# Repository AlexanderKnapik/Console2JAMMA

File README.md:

# Console2JAMMA

A system to plug video game consoles into a JAMMA arcade system. 

## Features & Goals
- SCART based RGB or VGA video input. Will work perfectly with any natively RGB or modded console, including the Dreamcast. Handles any sync stripping and CSYNC combination for you with amplified video.
- Works with any arcade cabinet supporting standard JAMMA, "CHAMMA" and the CPS2 kick harness.
- Stereo audio input with selectable mono audio combiner for the JAMMA edge, or an external stereo audio output. Amplified for up to 5 Watts of power and can handle standard arcade 4 Ohm or 8 Ohm speakers.
- Can drive 2 player controller ports for 5V or 3.3V based consoles. Will work with any console that has 12 or fewer IO lines with a modded controller port extension.
- Handy spring terminal controller adapters available for those not comfortable with soldering.
- Single player USB output to support PS3 or XBox360 too.

## Progress
This is still heavily a work in progress. I've built up the first hardware prototype and identified some issues that I would like to address. However I am mainly still testing the hardware.

There is also no firmware currently written yet. This is what would need to be addressed next before any further hardware prototypes are designed.

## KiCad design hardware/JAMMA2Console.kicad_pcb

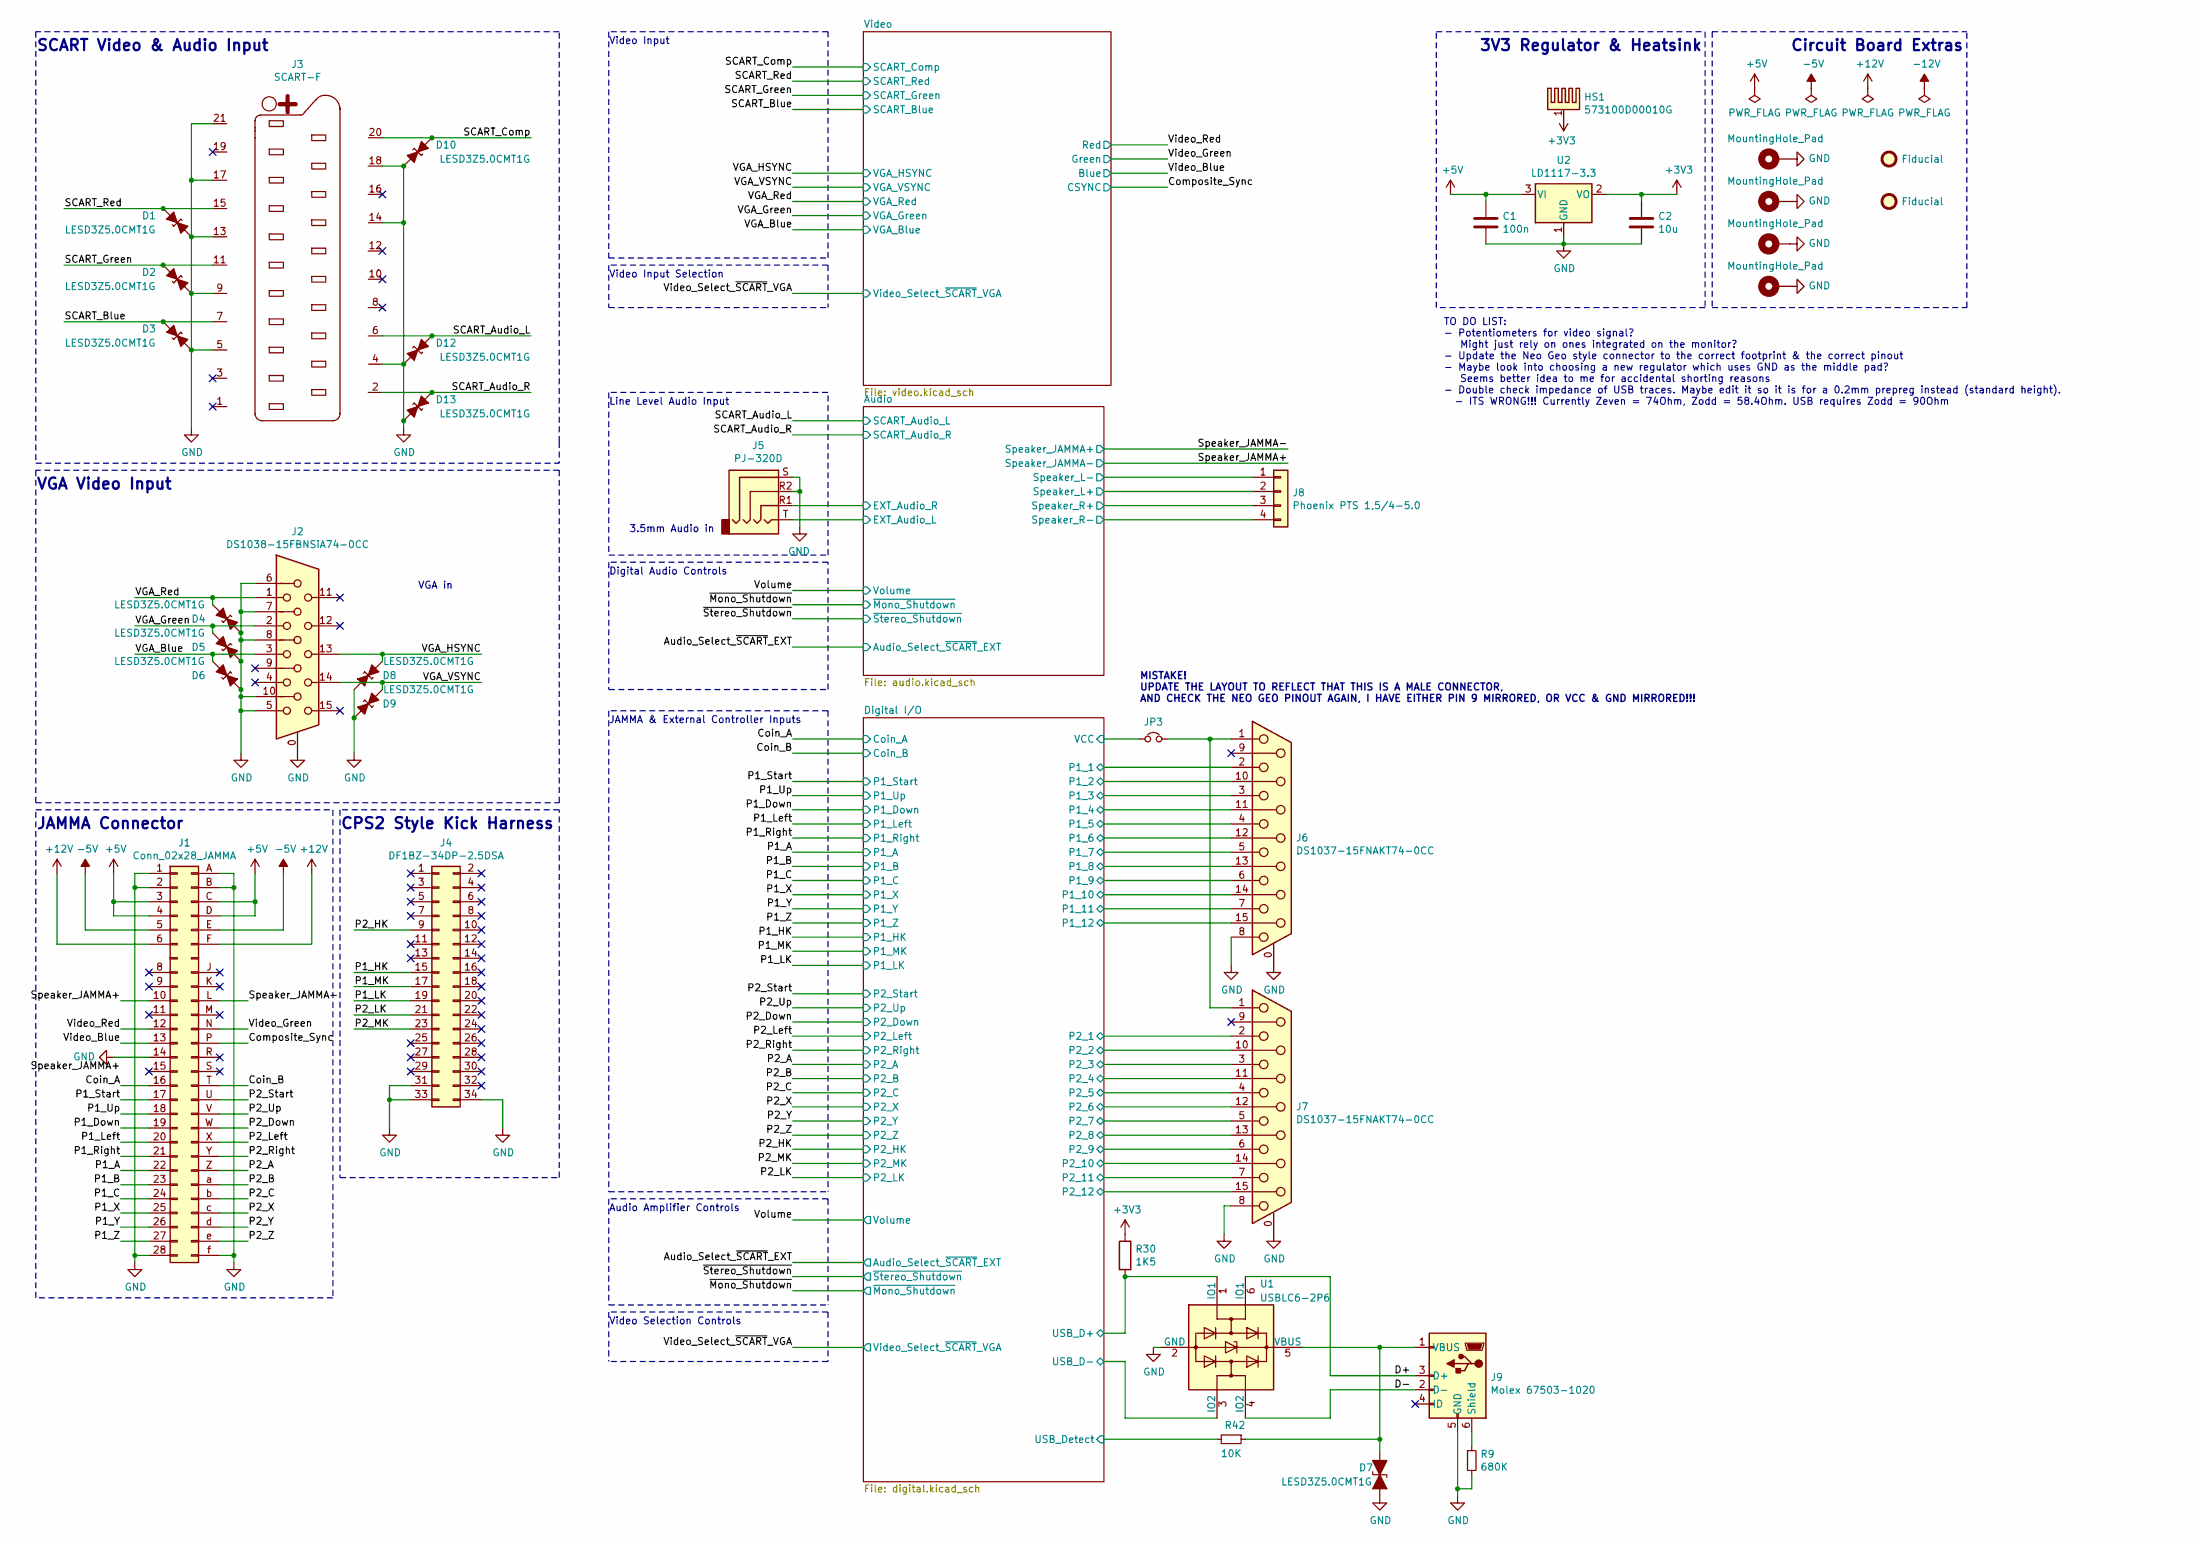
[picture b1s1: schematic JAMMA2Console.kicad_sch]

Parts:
C1: 100n; C_0603_1608Metric
C2: 10u; C_0805_2012Metric
D1, D2, D3, D4, D5, D6, D7, D8, D9, D10, D12, D13: LESD3Z5.0CMT1G; D_SOD-323
FID1, FID2: Fiducial; Fiducial_0.5mm_Mask1mm
H1, H2, H3, H4: MountingHole_Pad; MountingHole_3.2mm_M3_Pad_Via
HS1: 573100D00010G; Heatsink_AAVID_573100D000x0G_TO-252
J1: Conn_02x28_JAMMA; JAMMA_56_2x28_P3.96mm
J2: DS1038-15FBNSiA74-0CC; DSUB-15-HD_Female_Horizontal_P2.29x1.98mm_EdgePinOffset8.63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
J3: SCART-F; Conn_SCART_CS-107_Right_Angle_Female
J4: DF1BZ-34DP-2.5DSA; Conn_02x17_DF1BZ-34DP-2.5DSA
J5: PJ-320D; Jack_3.5mm_PJ320D_Horizontal
J6, J7: DS1037-15FNAKT74-0CC; DSUB-15_Female_Horizontal_P2.77x2.84mm_EdgePinOffset8.10mm_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
J8: Phoenix PTS 1,5/4-5.0; PhoenixContact_PTS_1,5_4-5_1x4_P5.00mm_Horizontal
J9: Molex 67503-1020; USB_Mini-B_Molex_657031020_Horizontal
JP3: Jumper_NC_Small; SolderJumper-2_P1.3mm_Open_TrianglePad1.0x1.5mm
R9: 680K; R_0603_1608Metric
R30: 1K5; R_0603_1608Metric
R42: 10K; R_0603_1608Metric
U1: USBLC6-2P6; SOT-666
U2: LD1117-3.3; TO-252-2

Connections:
+3V3: C2.1, HS1.1, R30.1, U2.2 (VO); also elsewhere on the board
+5V: C1.1, J1.3, J1.4, J1.C, J1.D, U2.3 (VI); also elsewhere on the board
+12V: J1.6, J1.F; also elsewhere on the board
-5V: J1.5, J1.E; also elsewhere on the board
/Coin_A: J1.16; also elsewhere on the board
/Coin_B: J1.T; also elsewhere on the board
/Composite_Sync: J1.P; also elsewhere on the board
/D+: J9.3 (D+), U1.6 (IO1)
/D-: J9.2 (D-), U1.4 (IO2)
/EXT_Audio_L: J5.T; also elsewhere on the board
/EXT_Audio_R: J5.R1; also elsewhere on the board
/P1_1: J6.2; also elsewhere on the board
/P1_2: J6.10; also elsewhere on the board
/P1_3: J6.3; also elsewhere on the board
/P1_4: J6.11 (P111); also elsewhere on the board
/P1_5: J6.4; also elsewhere on the board
/P1_6: J6.12; also elsewhere on the board
/P1_7: J6.5; also elsewhere on the board
/P1_8: J6.13; also elsewhere on the board
/P1_9: J6.6; also elsewhere on the board
/P1_10: J6.14; also elsewhere on the board
/P1_11: J6.7; also elsewhere on the board
/P1_12: J6.15; also elsewhere on the board
/P1_A: J1.22; also elsewhere on the board
/P1_B: J1.23; also elsewhere on the board
/P1_C: J1.24; also elsewhere on the board
/P1_Down: J1.19; also elsewhere on the board
/P1_HK: J4.15; also elsewhere on the board
/P1_LK: J4.19; also elsewhere on the board
/P1_Left: J1.20; also elsewhere on the board
/P1_MK: J4.17; also elsewhere on the board
/P1_Right: J1.21; also elsewhere on the board
/P1_Start: J1.17; also elsewhere on the board
/P1_Up: J1.18; also elsewhere on the board
/P1_X: J1.25; also elsewhere on the board
/P1_Y: J1.26; also elsewhere on the board
/P1_Z: J1.27; also elsewhere on the board
/P2_1: J7.2; also elsewhere on the board
/P2_2: J7.10; also elsewhere on the board
/P2_3: J7.3; also elsewhere on the board
/P2_4: J7.11 (P111); also elsewhere on the board
/P2_5: J7.4; also elsewhere on the board
/P2_6: J7.12; also elsewhere on the board
/P2_7: J7.5; also elsewhere on the board
/P2_8: J7.13; also elsewhere on the board
/P2_9: J7.6; also elsewhere on the board
/P2_10: J7.14; also elsewhere on the board
/P2_11: J7.7; also elsewhere on the board
/P2_12: J7.15; also elsewhere on the board
/P2_A: J1.Z; also elsewhere on the board
/P2_B: J1.a; also elsewhere on the board
/P2_C: J1.b; also elsewhere on the board
/P2_Down: J1.W; also elsewhere on the board
/P2_HK: J4.9; also elsewhere on the board
/P2_LK: J4.21; also elsewhere on the board
/P2_Left: J1.X; also elsewhere on the board
/P2_MK: J4.23; also elsewhere on the board
/P2_Right: J1.Y; also elsewhere on the board
/P2_Start: J1.U; also elsewhere on the board
/P2_Up: J1.V; also elsewhere on the board
/P2_X: J1.c; also elsewhere on the board
/P2_Y: J1.d; also elsewhere on the board
/P2_Z: J1.e; also elsewhere on the board
/SCART_Audio_L: D12.1, J3.6; also elsewhere on the board
/SCART_Audio_R: D13.1, J3.2; also elsewhere on the board
/SCART_Blue: D3.1, J3.7; also elsewhere on the board
/SCART_Comp: D10.1, J3.20; also elsewhere on the board
/SCART_Green: D2.1, J3.11; also elsewhere on the board
/SCART_Red: D1.1, J3.15; also elsewhere on the board
/Speaker_JAMMA+: J1.10; also elsewhere on the board
/Speaker_JAMMA-: J1.L; also elsewhere on the board
/Speaker_L+: J8.2; also elsewhere on the board
/Speaker_L-: J8.1; also elsewhere on the board
/Speaker_R+: J8.3; also elsewhere on the board
/Speaker_R-: J8.4; also elsewhere on the board
/USB_D+: R30.2, U1.1 (IO1); also elsewhere on the board
/USB_D-: U1.3 (IO2); also elsewhere on the board
/USB_Detect: R42.2; also elsewhere on the board
/VCC: JP3.2; also elsewhere on the board
/VGA_Blue: D6.2, J2.3; also elsewhere on the board
/VGA_Green: D5.2, J2.2; also elsewhere on the board
/VGA_HSYNC: D8.2, J2.13; also elsewhere on the board
/VGA_Red: D4.2, J2.1; also elsewhere on the board
/VGA_VSYNC: D9.2, J2.14; also elsewhere on the board
/Video_Blue: J1.13; also elsewhere on the board
/Video_Green: J1.N; also elsewhere on the board
/Video_Red: J1.12; also elsewhere on the board
GND: C1.2, C2.2, D1.2, D2.2, D3.2, D4.1, D5.1, D6.1, D7.2 (A2), D8.1, D9.1, D10.2, D12.2, D13.2, H1.1, H2.1, H3.1, H4.1, J1.1, J1.2, J1.14, J1.28, J1.A, J1.B, J1.f, J2.0, J2.5, J2.6, J2.7, J2.8, J2.10, J3.4, J3.5, J3.9, J3.13, J3.14, J3.17, J3.18, J3.21, J4.31, J4.33, J4.34, J5.R2, J5.S, J6.0 (PAD), J6.8, J7.0 (PAD), J7.8, J9.5 (GND), R9.2, U1.2 (GND), U2.1 (GND); also elsewhere on the board
unnamed: D7.1 (A1), J9.1 (VBUS), R42.1, U1.5 (VBUS)
unnamed: J6.1, J7.1, JP3.1
unnamed: J9.6 (Shield), R9.1

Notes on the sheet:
SCART Video & Audio Input
VGA Video Input
JAMMA Connector
CPS2 Style Kick Harness
VGA in
Video Input
Video Input Selection
Line Level Audio Input
Digital Audio Controls
JAMMA & External Controller Inputs
Audio Amplifier Controls
Video Selection Controls
3.5mm Audio in
MISTAKE! UPDATE THE LAYOUT TO REFLECT THAT THIS IS A MALE CONNECTOR, AND CHECK THE NEO GEO PINOUT AGAIN, I HAVE EITHER PIN 9 MIRRORED, OR VCC & GND MIRRORED!!!
TO DO LIST: - Potentiometers for video signal? Might just rely on ones integrated on the monitor? - Update the Neo Geo style connector to the correct footprint & the correct pinout - Maybe look into choosing a new regulator which uses GND as the middle pad? Seems better idea to me for accidental sh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
3V3 Regulator & Heatsink
Circuit Board Extras

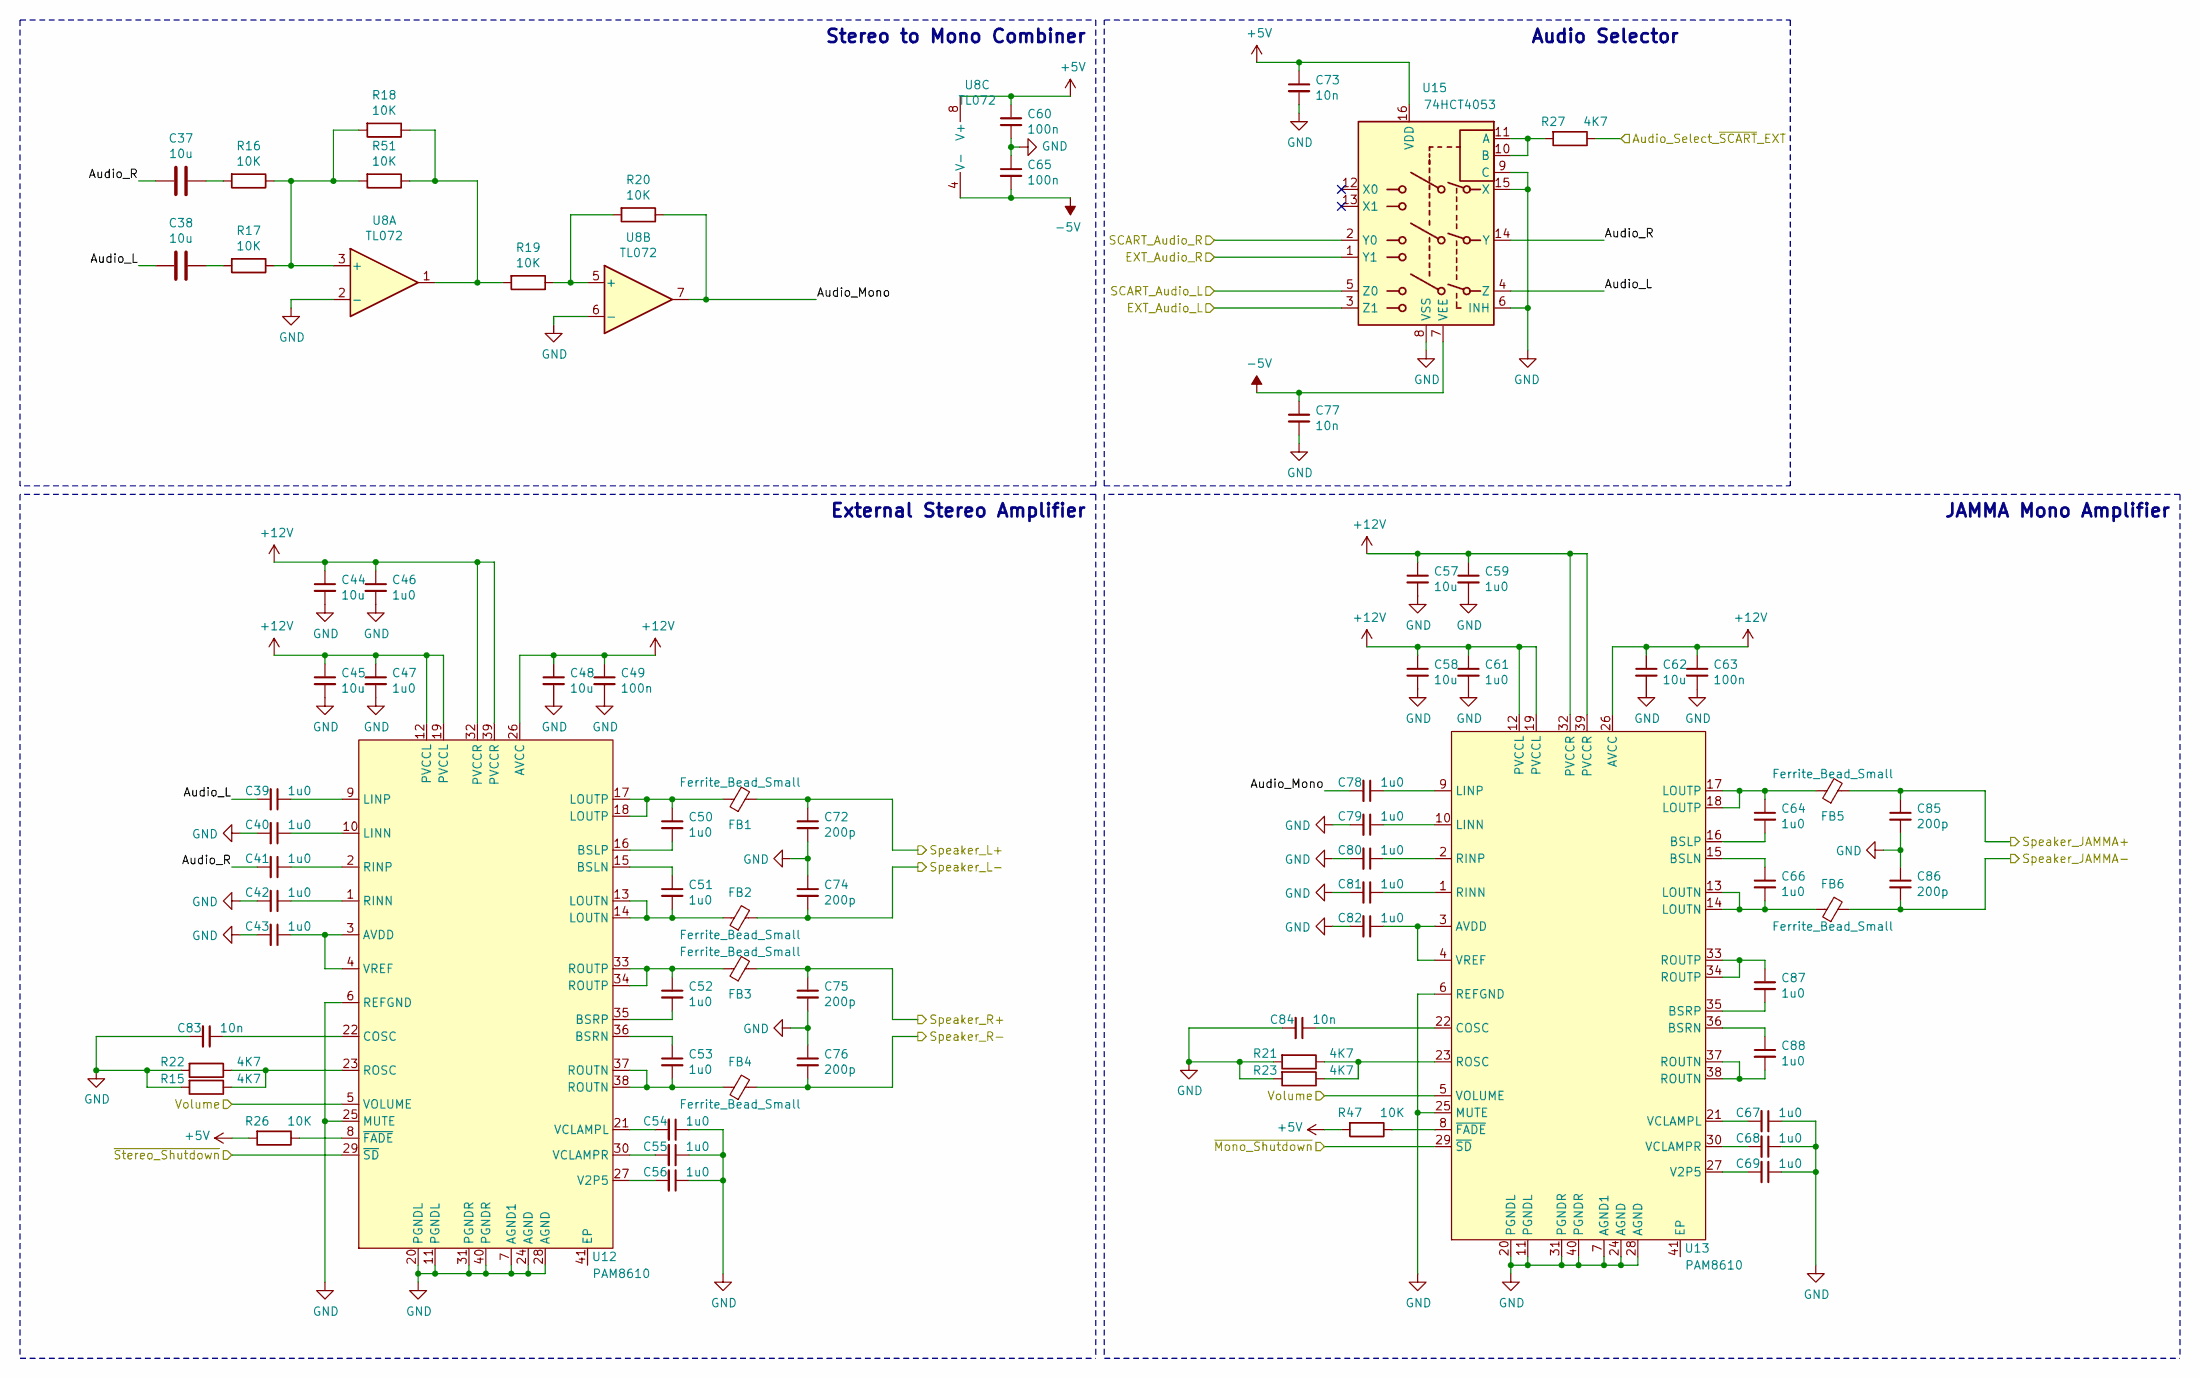
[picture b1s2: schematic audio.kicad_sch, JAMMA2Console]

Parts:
C37, C38, C44, C45, C48, C57, C58, C62: 10u; C_0805_2012Metric
C39, C40, C41, C42, C43, C46, C47, C50, C51, C52, C53, C54, C55, C56, C59, C61, C64, C66, C67, C68, C69, C78, C79, C80, C81, C82, C87, C88: 1u0; C_0603_1608Metric
C49, C60, C63, C65: 100n; C_0603_1608Metric
C72, C74, C75, C76, C85, C86: 200p; C_0603_1608Metric
C73, C77, C83, C84: 10n; C_0603_1608Metric
FB1, FB2, FB3, FB4, FB5, FB6: Ferrite_Bead_Small; L_0603_1608Metric
R15, R21, R22, R23, R27: 4K7; R_0603_1608Metric
R16, R17, R18, R19, R20, R26, R47, R51: 10K; R_0603_1608Metric
U8: TL072; SOIC-8_3.9x4.9mm_P1.27mm
U12, U13: PAM8610; QFN-40-1EP_6x6mm_P0.5mm_EP4.6x4.6mm_ThermalVias
U15: 74HCT4053; SSOP-16_5.3x6.2mm_P0.65mm

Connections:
+5V: C60.1, C73.1, R26.2, R47.2, U8.8 (V+), U15.16 (VDD); also elsewhere on the board
+12V: C44.1, C45.1, C46.1, C47.1, C48.1, C49.1, C57.1, C58.1, C59.1, C61.1, C62.1, C63.1, U12.12 (PVCCL), U12.19 (PVCCL), U12.26 (AVCC), U12.32 (PVCCR), U12.39 (PVCCR), U13.12 (PVCCL), U13.19 (PVCCL), U13.26 (AVCC), U13.32 (PVCCR), U13.39 (PVCCR); also elsewhere on the board
-5V: C65.2, C77.1, U8.4 (V-), U15.7 (VEE); also elsewhere on the board
/Audio/Audio_L: C38.2, C39.2, U15.4 (Z)
/Audio/Audio_Mono: C78.2, R20.1, U8.7
/Audio/Audio_R: C37.2, C41.2, U15.14 (Y)
/Audio_Select_~SCART~_EXT: R27.1; also elsewhere on the board
/EXT_Audio_L: U15.3 (Z1); also elsewhere on the board
/EXT_Audio_R: U15.1 (Y1); also elsewhere on the board
/SCART_Audio_L: U15.5 (Z0); also elsewhere on the board
/SCART_Audio_R: U15.2 (Y0); also elsewhere on the board
/Speaker_JAMMA+: C86.2, FB6.2; also elsewhere on the board
/Speaker_JAMMA-: C85.1, FB5.2; also elsewhere on the board
/Speaker_L+: C72.1, FB1.2; also elsewhere on the board
/Speaker_L-: C74.2, FB2.2; also elsewhere on the board
/Speaker_R+: C75.1, FB3.2; also elsewhere on the board
/Speaker_R-: C76.2, FB4.2; also elsewhere on the board
/Volume: U12.5 (VOLUME), U13.5 (VOLUME); also elsewhere on the board
/~Mono_Shutdown~: U13.29 (~SD~); also elsewhere on the board
/~Stereo_Shutdown~: U12.29 (~SD~); also elsewhere on the board
GND: C40.2, C42.2, C43.2, C44.2, C45.2, C46.2, C47.2, C48.2, C49.2, C54.1, C55.1, C56.1, C57.2, C58.2, C59.2, C60.2, C61.2, C62.2, C63.2, C65.1, C67.1, C68.1, C69.1, C72.2, C73.2, C74.1, C75.2, C76.1, C77.2, C79.2, C80.2, C81.2, C82.2, C83.2, C84.2, C85.2, C86.1, R15.2, R21.2, R22.2, R23.2, U8.2 (-), U8.6 (-), U12.6 (REFGND), U12.7 (AGND1), U12.11 (PGNDL), U12.20 (PGNDL), U12.24 (AGND), U12.25 (MUTE), U12.28 (AGND), U12.31 (PGNDR), U12.40 (PGNDR), U13.6 (REFGND), U13.7 (AGND1), U13.11 (PGNDL), U13.20 (PGNDL), U13.24 (AGND), U13.25 (MUTE), U13.28 (AGND), U13.31 (PGNDR), U13.40 (PGNDR), U15.6 (INH), U15.8 (VSS), U15.9 (C), U15.15 (X); also elsewhere on the board
unnamed: C37.1, R16.2
unnamed: C38.1, R17.2
unnamed: C39.1, U12.9 (LINP)
unnamed: C40.1, U12.10 (LINN)
unnamed: C41.1, U12.2 (RINP)
unnamed: C42.1, U12.1 (RINN)
unnamed: C43.1, U12.3 (AVDD), U12.4 (VREF)
unnamed: C50.1, FB1.1, U12.17 (LOUTP), U12.18 (LOUTP)
unnamed: C50.2, U12.16 (BSLP)
unnamed: C51.1, U12.15 (BSLN)
unnamed: C51.2, FB2.1, U12.13 (LOUTN), U12.14 (LOUTN)
unnamed: C52.1, FB3.1, U12.33 (ROUTP), U12.34 (ROUTP)
unnamed: C52.2, U12.35 (BSRP)
unnamed: C53.1, U12.36 (BSRN)
unnamed: C53.2, FB4.1, U12.37 (ROUTN), U12.38 (ROUTN)
unnamed: C54.2, U12.21 (VCLAMPL)
unnamed: C55.2, U12.30 (VCLAMPR)
unnamed: C56.2, U12.27 (V2P5)
unnamed: C64.1, FB5.1, U13.17 (LOUTP), U13.18 (LOUTP)
unnamed: C64.2, U13.16 (BSLP)
unnamed: C66.1, U13.15 (BSLN)
unnamed: C66.2, FB6.1, U13.13 (LOUTN), U13.14 (LOUTN)
unnamed: C67.2, U13.21 (VCLAMPL)
unnamed: C68.2, U13.30 (VCLAMPR)
unnamed: C69.2, U13.27 (V2P5)
unnamed: C78.1, U13.9 (LINP)
unnamed: C79.1, U13.10 (LINN)
unnamed: C80.1, U13.2 (RINP)
unnamed: C81.1, U13.1 (RINN)
unnamed: C82.1, U13.3 (AVDD), U13.4 (VREF)
unnamed: C83.1, U12.22 (COSC)
unnamed: C84.1, U13.22 (COSC)
unnamed: C87.1, U13.33 (ROUTP), U13.34 (ROUTP)
unnamed: C87.2, U13.35 (BSRP)
unnamed: C88.1, U13.36 (BSRN)
unnamed: C88.2, U13.37 (ROUTN), U13.38 (ROUTN)
unnamed: R15.1, R22.1, U12.23 (ROSC)
unnamed: R16.1, R17.1, R18.2, R51.2, U8.3 (+)
unnamed: R18.1, R19.2, R51.1, U8.1
unnamed: R19.1, R20.2, U8.5 (+)
unnamed: R21.1, R23.1, U13.23 (ROSC)
unnamed: R26.1, U12.8 (~FADE~)
unnamed: R27.2, U15.10 (B), U15.11 (A)
unnamed: R47.1, U13.8 (~FADE~)

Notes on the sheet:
Stereo to Mono Combiner
External Stereo Amplifier
Audio Selector
JAMMA Mono Amplifier

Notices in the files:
hardware/JAMMA2Console Adapter/JAMMA2Console Adapter.kicad_pcb:
CERN-OHL-S v2
hardware/JAMMA2Console.kicad_pcb:
Licensed under CERN-OHL-S v2
